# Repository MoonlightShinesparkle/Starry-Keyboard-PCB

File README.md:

# Starry keyboard PCB files
A KiCad board which allows for the direct insertion or soldering of an appropriate Raspberry Pico model (the project was based in the 2W model, however a W might work) to allow the direct use of the Starry Keyboard code project. The board is based in the concept of a button matrix, allowing for the usage of 25 buttons with only 10 GPIOs from the pico, the rest being used to communicate with an EEPROM and LEDs, the project is directly based in the Moonlit Keyboard project.

# Components
The board is based in the mix of SMD and THT components, most notable SMD components being a capacitor, pull up resistors, power resistors and LEDs, meanwhile the rest of the components are THT and some were meant to be soldered with a base or with pin header sockets to allow for the easy insertion of the components and simple removal process from the board, allowing the use of the microcontroller board for other uses.

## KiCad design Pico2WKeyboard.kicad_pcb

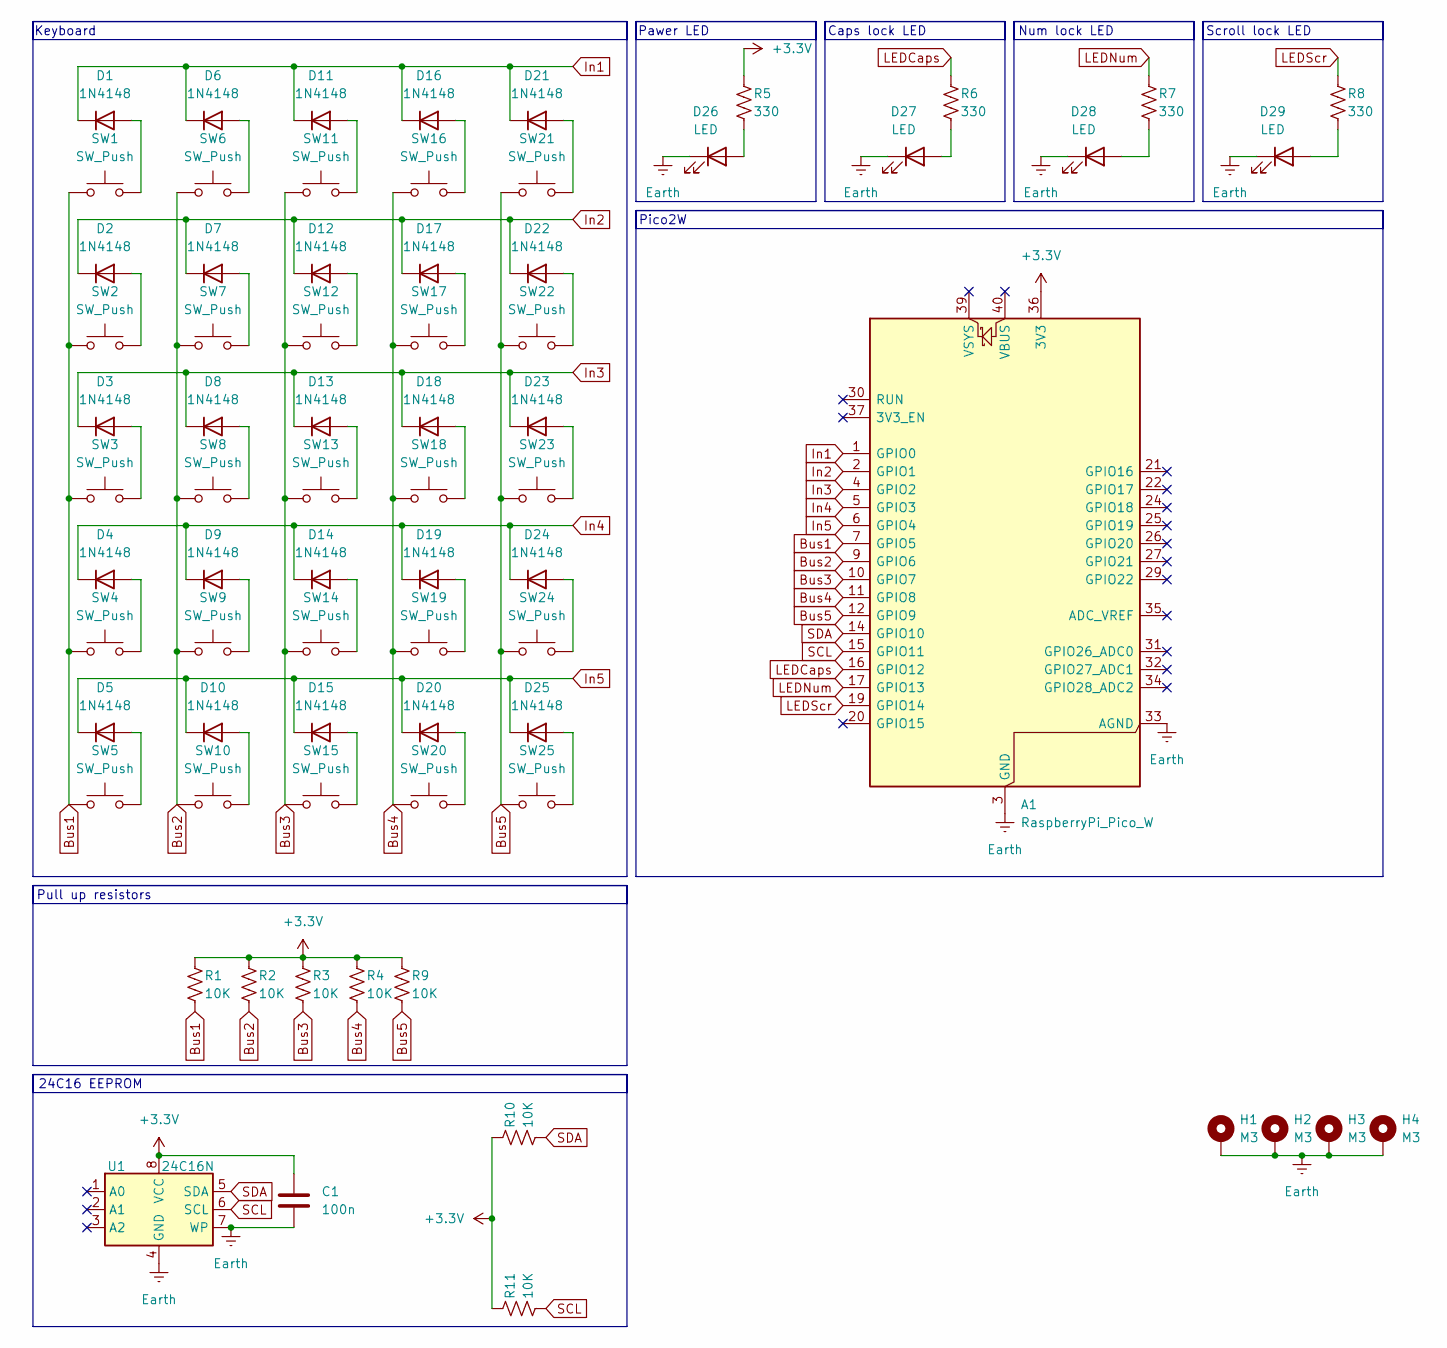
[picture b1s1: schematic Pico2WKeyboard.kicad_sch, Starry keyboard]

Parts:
A1: RaspberryPi_Pico_W; RaspberryPi_Pico_Common_Unspecified; LCSC C42394205
C1: 100n; C_0402_1005Metric_Pad0.74x0.62mm_HandSolder; LCSC C1525
D1, D2, D3, D4, D5, D6, D7, D8, D9, D10, D11, D12, D13, D14, D15, D16, D17, D18, D19, D20, D21, D22, D23, D24, D25: 1N4148; D_DO-35_SOD27_P7.62mm_Horizontal; LCSC C402212
D26: LED; LED_0603_1608Metric_Pad1.05x0.95mm_HandSolder; LCSC C389522
D27, D28, D29: LED; LED_0603_1608Metric_Pad1.05x0.95mm_HandSolder; LCSC C2286
H1, H2, H3, H4: M3; MountingHole_3.2mm_M3_Pad_Via
R1, R2, R3, R4, R9, R10, R11: 10K; R_0603_1608Metric_Pad0.98x0.95mm_HandSolder; LCSC C25804
R5, R6, R7, R8: 330; R_0603_1608Metric_Pad0.98x0.95mm_HandSolder; LCSC C23138
SW1, SW2, SW3, SW4, SW5, SW6, SW7, SW8, SW9, SW10, SW11, SW12, SW13, SW14, SW15, SW16, SW17, SW18, SW19, SW20, SW21, SW22, SW23, SW24, SW25: SW_Push; SW_PUSH_6mm; LCSC C393938
U1: 24C16N; DIP-8_W7.62mm_Socket; LCSC C18723551

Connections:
+3.3V: A1.36 (3V3), C1.1, R1.1, R2.1, R3.1, R4.1, R5.1, R9.1, R10.1, R11.1, U1.8 (VCC)
Bus1: A1.7 (GPIO5), R1.2, SW1.1, SW2.1, SW3.1, SW4.1, SW5.1
Bus2: A1.9 (GPIO6), R2.2, SW6.1, SW7.1, SW8.1, SW9.1, SW10.1
Bus3: A1.10 (GPIO7), R3.2, SW11.1, SW12.1, SW13.1, SW14.1, SW15.1
Bus4: A1.11 (GPIO8), R4.2, SW16.1, SW17.1, SW18.1, SW19.1, SW20.1
Bus5: A1.12 (GPIO9), R9.2, SW21.1, SW22.1, SW23.1, SW24.1, SW25.1
Earth: A1.3 (GND), A1.8 (GND), A1.13 (GND), A1.18 (GND), A1.23 (GND), A1.28 (GND), A1.33 (AGND), A1.38 (GND), C1.2, D26.1 (K), D27.1 (K), D28.1 (K), D29.1 (K), H1.1 (1_1), H2.1 (1_1), H3.1 (1_1), H4.1 (1_1), U1.4 (GND), U1.7 (WP)
In1: A1.1 (GPIO0), D1.1 (K), D6.1 (K), D11.1 (K), D16.1 (K), D21.1 (K)
In2: A1.2 (GPIO1), D2.1 (K), D7.1 (K), D12.1 (K), D17.1 (K), D22.1 (K)
In3: A1.4 (GPIO2), D3.1 (K), D8.1 (K), D13.1 (K), D18.1 (K), D23.1 (K)
In4: A1.5 (GPIO3), D4.1 (K), D9.1 (K), D14.1 (K), D19.1 (K), D24.1 (K)
In5: A1.6 (GPIO4), D5.1 (K), D10.1 (K), D15.1 (K), D20.1 (K), D25.1 (K)
LEDCaps: A1.16 (GPIO12), R6.1
LEDNum: A1.17 (GPIO13), R7.1
LEDScr: A1.19 (GPIO14), R8.1
unnamed: D1.2 (A), SW1.2
unnamed: D2.2 (A), SW2.2
unnamed: D3.2 (A), SW3.2
unnamed: D4.2 (A), SW4.2
unnamed: D5.2 (A), SW5.2
unnamed: D6.2 (A), SW6.2
unnamed: D7.2 (A), SW7.2
unnamed: D8.2 (A), SW8.2
unnamed: D9.2 (A), SW9.2
unnamed: D10.2 (A), SW10.2
unnamed: D11.2 (A), SW11.2
unnamed: D12.2 (A), SW12.2
unnamed: D13.2 (A), SW13.2
unnamed: D14.2 (A), SW14.2
unnamed: D15.2 (A), SW15.2
unnamed: D16.2 (A), SW16.2
unnamed: D17.2 (A), SW17.2
unnamed: D18.2 (A), SW18.2
unnamed: D19.2 (A), SW19.2
unnamed: D20.2 (A), SW20.2
unnamed: D21.2 (A), SW21.2
unnamed: D22.2 (A), SW22.2
unnamed: D23.2 (A), SW23.2
unnamed: D24.2 (A), SW24.2
unnamed: D25.2 (A), SW25.2
unnamed: D26.2 (A), R5.2
unnamed: D27.2 (A), R6.2
unnamed: D28.2 (A), R7.2
unnamed: D29.2 (A), R8.2
SCL: A1.15 (GPIO11), R11.2, U1.6 (SCL)
SDA: A1.14 (GPIO10), R10.2, U1.5 (SDA)

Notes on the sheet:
Num lock LED
Pico2W
24C16 EEPROM
Scroll lock LED
Keyboard
Caps lock LED
Pull up resistors
Pawer LED

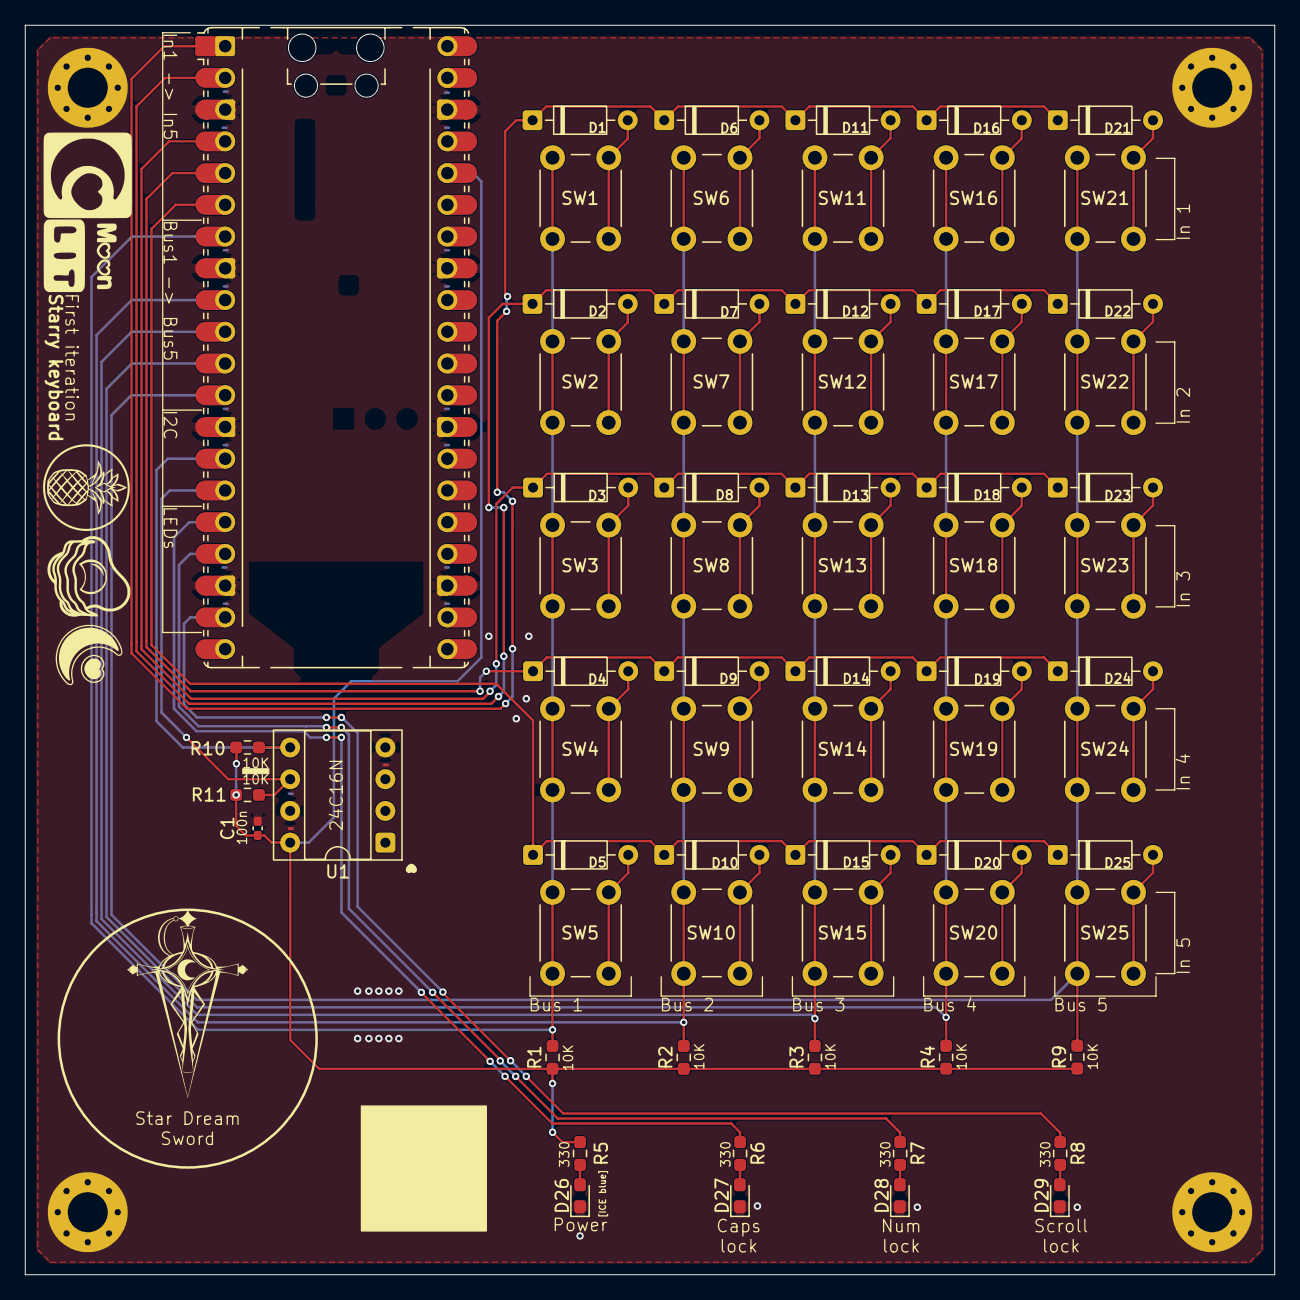
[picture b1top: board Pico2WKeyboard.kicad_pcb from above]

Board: 2 copper layers, 100.0 x 100.0 mm, 72 parts (0 on the bottom side), 46 nets.

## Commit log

2026-04-22 File upload .w.
2026-04-22 Added LCSC numbers
2026-04-22 Added license
